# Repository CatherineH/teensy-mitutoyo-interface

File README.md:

# teensy-mitutoyo-interface
An interface to Mitutoyo dial indicators from a teensy

Originally based off of an [instructable](http://www.instructables.com/id/Interfacing-a-Digital-Micrometer-to-a-Microcontrol/) by [Steve Spence](http://arduinotronics.blogspot.com/).

For more details, check out [my blog post](http://catherineh.github.io/programming/2016/09/21/teensy-mitutoyo-interface.html) about this project.

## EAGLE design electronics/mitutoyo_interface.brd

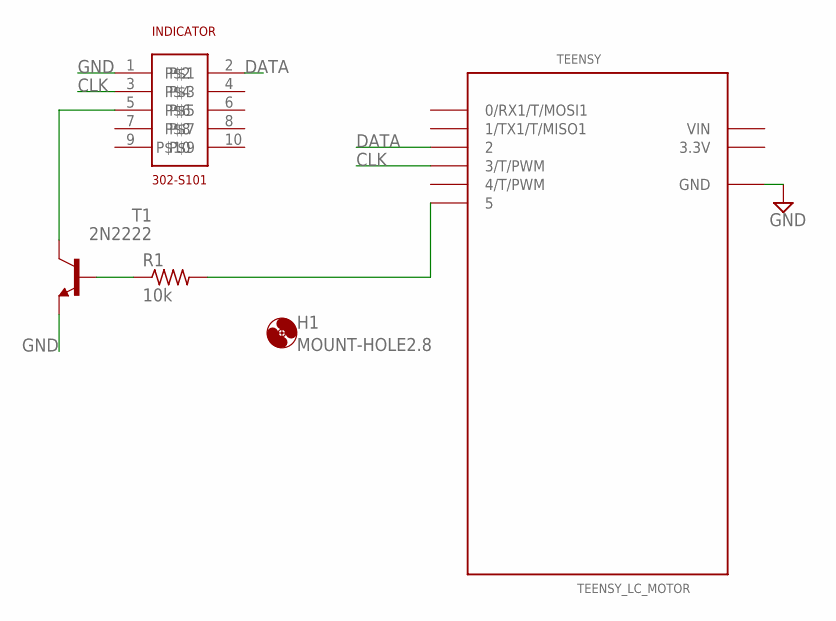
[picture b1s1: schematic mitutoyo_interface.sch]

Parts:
H1: MOUNT-HOLE2.8; 2,8
INDICATOR: 302-S101
R1: 10k; R0805
T1: 2N2222; TO92-EBC-OVAL
TEENSY: TEENSY_LC_MOTOR; TEENSYLC-MOTOR

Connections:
3.3V: TEENSY.3.3V
CLK: INDICATOR.3, TEENSY.3 (3/T/PWM)
DATA: INDICATOR.2, TEENSY.2
GND: INDICATOR.1, T1.E, TEENSY.GND
unnamed: INDICATOR.5, T1.C
unnamed: R1.1, T1.B
unnamed: R1.2, TEENSY.5
VIN: TEENSY.VIN

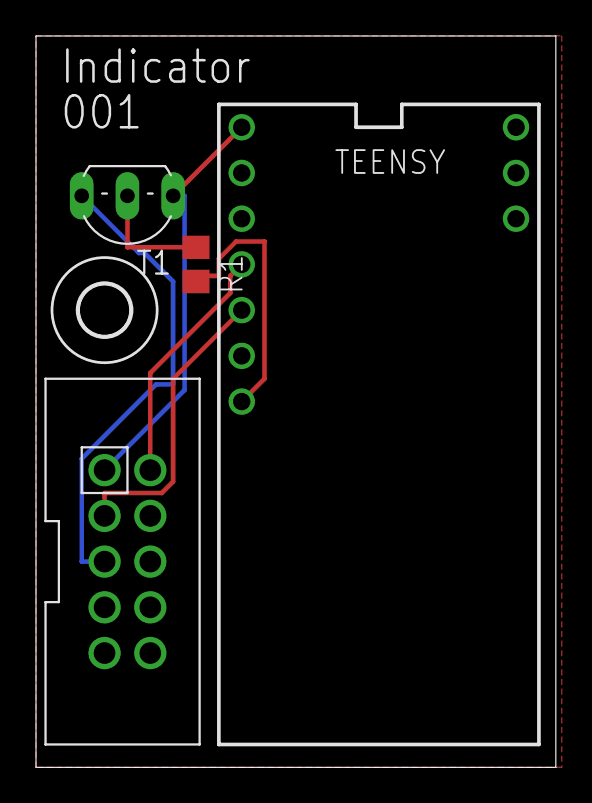
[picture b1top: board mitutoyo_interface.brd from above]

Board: 2 copper layers, 28.9 x 40.6 mm, 5 parts (0 on the bottom side), 6 nets.

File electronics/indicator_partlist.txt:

Partlist

Exported from mitsuyo_interface.sch at 8/31/16 2:12 PM

EAGLE Version 7.5.0 Copyright (c) 1988-2015 CadSoft

Assembly variant: 

Part      Value           Device          Package        Library                            Sheet

INDICATOR 302-S101        302-S101        302-S101       connectors                         1
R1        10k             R-US_R0805      R0805          resistor                           1
T1        2N2222          2N2222          TO92-EBC-OVAL  adafruit                           1
TEENSY    TEENSY_LC_MOTOR TEENSY_LC_MOTOR TEENSYLC-MOTOR Teensy_3_and_LC_Series_Boards_v1.1 1

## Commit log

2016-09-21 added source code
2016-09-22 added blog post to readme
2016-09-22 added setup.py file
2016-09-22 fixed setup file
2016-09-23 added error check
